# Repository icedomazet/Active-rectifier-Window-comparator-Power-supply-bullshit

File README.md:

Good fucking luck, You're on your own.

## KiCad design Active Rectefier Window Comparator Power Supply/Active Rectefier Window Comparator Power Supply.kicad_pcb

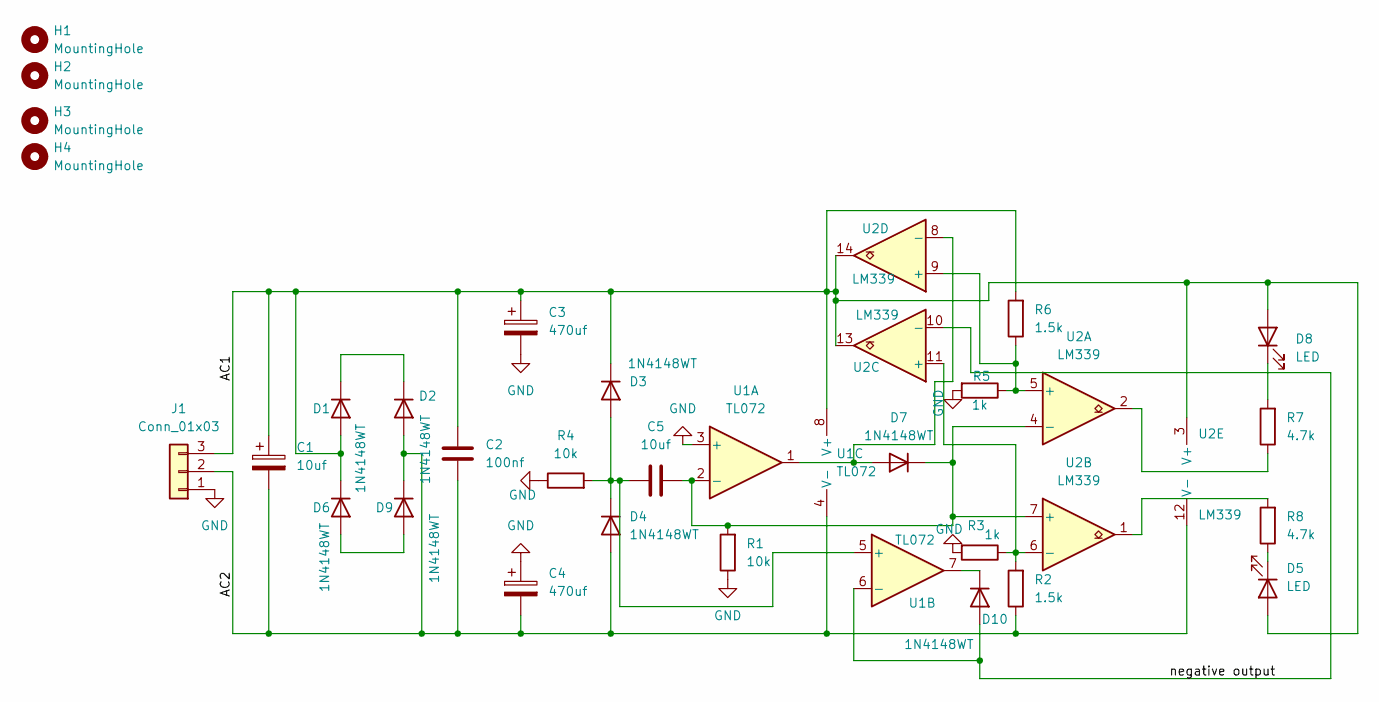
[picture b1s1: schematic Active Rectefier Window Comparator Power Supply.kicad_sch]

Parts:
C1: 10uf; CP_Radial_D4.0mm_P2.00mm
C2: 100nf; C_Disc_D5.0mm_W2.5mm_P2.50mm
C3, C4: 470uf; CP_Radial_D4.0mm_P2.00mm
C5: 10uf; C_Disc_D5.0mm_W2.5mm_P2.50mm
D1, D2, D3, D4, D6, D7, D9, D10: 1N4148WT; D_5W_P12.70mm_Horizontal
D5, D8: LED; LED_D5.0mm
H1, H2, H3, H4: MountingHole; MountingHole_2.7mm_M2.5_ISO14580
J1: Conn_01x03; TerminalBlock_MaiXu_MX126-5.0-03P_1x03_P5.00mm
R1, R4: 10k; R_Axial_DIN0207_L6.3mm_D2.5mm_P10.16mm_Horizontal
R2, R6: 1.5k; R_Axial_DIN0207_L6.3mm_D2.5mm_P10.16mm_Horizontal
R3, R5: 1k; R_Axial_DIN0207_L6.3mm_D2.5mm_P10.16mm_Horizontal
R7, R8: 4.7k; R_Axial_DIN0207_L6.3mm_D2.5mm_P10.16mm_Horizontal
U1: TL072; DIP-8_W7.62mm_LongPads
U2: LM339; DIP-14_W7.62mm_LongPads

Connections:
/AC1: C1.1, C2.1, C3.1, D1.2 (A), D3.1 (K), D5.2 (A), D6.1 (K), D8.2 (A), J1.3, R6.2, U1.8 (V+), U2.3 (V+), U2.13, U2.14
/AC2: C1.2, C2.2, C4.2, D2.2 (A), D4.2 (A), D9.1 (K), J1.2, R2.1, U1.4 (V-), U2.12 (V-)
/negative output: D10.2 (A), U1.6 (-), U2.10 (-)
GND: C3.2, C4.1, J1.1, R1.1, R3.2, R4.1, R5.2, U1.3 (+)
unnamed: D1.1 (K), D2.1 (K)
unnamed: C5.1, D3.2 (A), D4.1 (K), R4.2, U1.5 (+)
unnamed: D5.1 (K), R8.1
unnamed: D6.2 (A), D9.2 (A)
unnamed: D7.2 (A), U1.1, U2.8 (-)
unnamed: C5.2, D7.1 (K), R1.2, U1.2 (-), U2.4 (-), U2.7 (+)
unnamed: D8.1 (K), R7.2
unnamed: D10.1 (K), U1.7
unnamed: R7.1, U2.2
unnamed: R8.2, U2.1
unnamed: R5.1, R6.1, U2.5 (+), U2.9 (+)
unnamed: R2.2, R3.1, U2.6 (-), U2.11 (+)

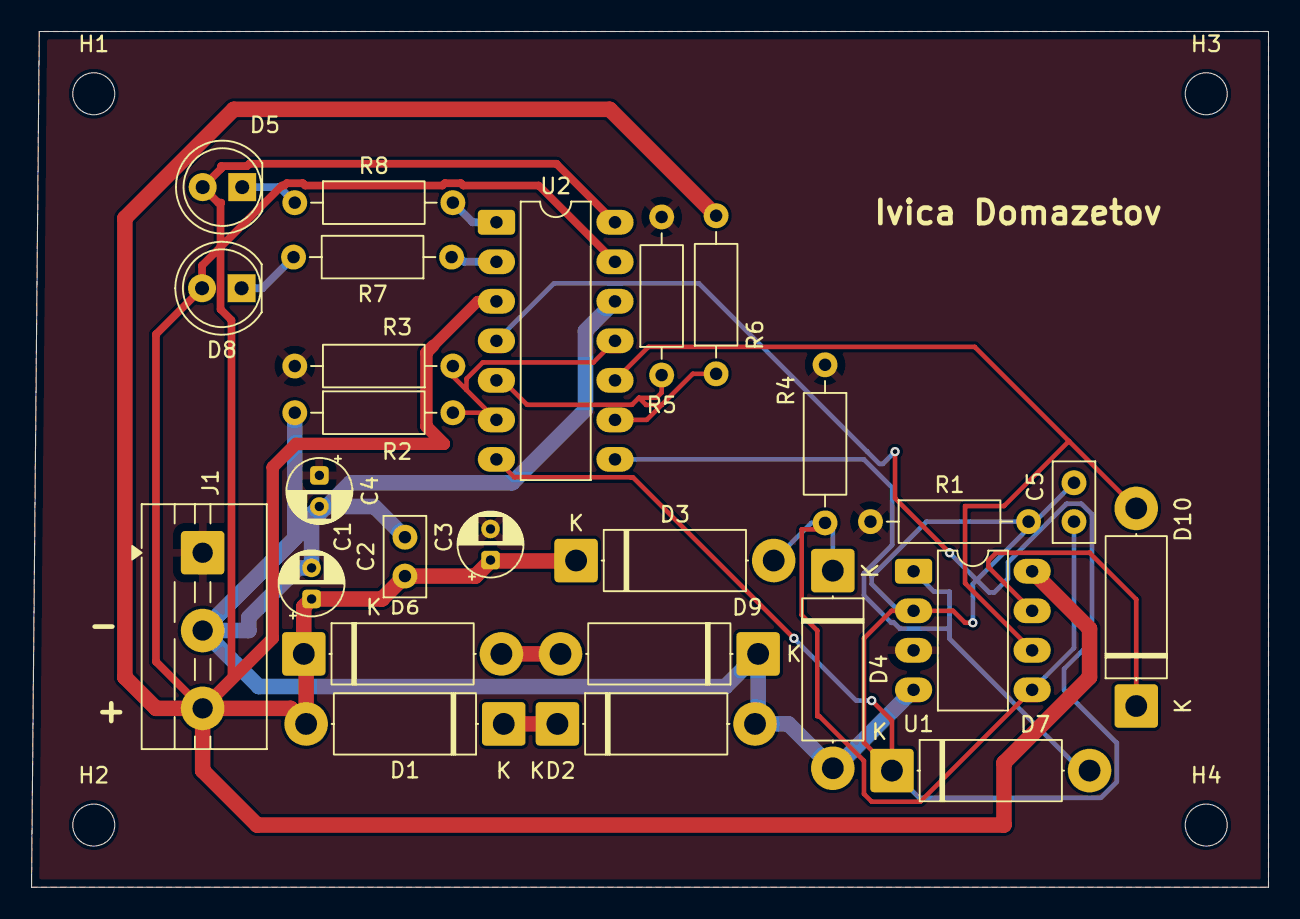
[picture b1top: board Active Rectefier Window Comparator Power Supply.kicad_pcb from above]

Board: 2 copper layers, 79.5 x 55.0 mm, 30 parts (0 on the bottom side), 16 nets.
